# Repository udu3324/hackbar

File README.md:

# hackbar

Hackbar is a macro keys pad in the shape of a bar designed to be placed on the long side of your keyboard. It features 7 switches, an encoder, and two neopixels per key and encoder. It is also inspired by the [Google g-board april fools video](https://www.youtube.com/watch?v=9G3DWHf1xX0). 

# firmware

KMK firmware is used to tell what the mcu sends to the host device when recieving switch inputs. 

# CAD

The cad can be found on [onshape](https://cad.onshape.com/documents/5cba3b888e11db533a85f54f/w/c697cc47e3473bff9588772d/e/0aef22490cba32d3fbb4fb29?renderMode=0&uiState=698d35e3e8867af81a3cb232). 

# Why I Made It

I wanted a macro keyboard that felt like the media control boards used in the a/v industry. They feature toggled leds that are vibrant and bright and look satisfying. I also would like to share this board with some of my friends as its very simple and easy to understand.

# How to Use 

The Seeed Xiao RP2040 makes flashing code very easy through circuitpython on the usb-c. 

# Photos

# Bill of Materials

|Part              |Quantity|On hand|Price |
|------------------|--------|-------|------|
|DSA Keycaps       |7       |no     |      |
|Switches          |7       |no     |      |
|Rotary Encoder Cap|1       |no     |      |
|Rotary Encoder    |1       |no     |      |
|SK6812 MINI-E LEDs|16      |no     |      |
|PCB               |        |no     |$9.55 |
|Seeed XIAO RP2040 |1       |no     |      |
|3d Printed Case   |1       |yes    |      |
|Hot-swap Socket   |7       |yes    |      |

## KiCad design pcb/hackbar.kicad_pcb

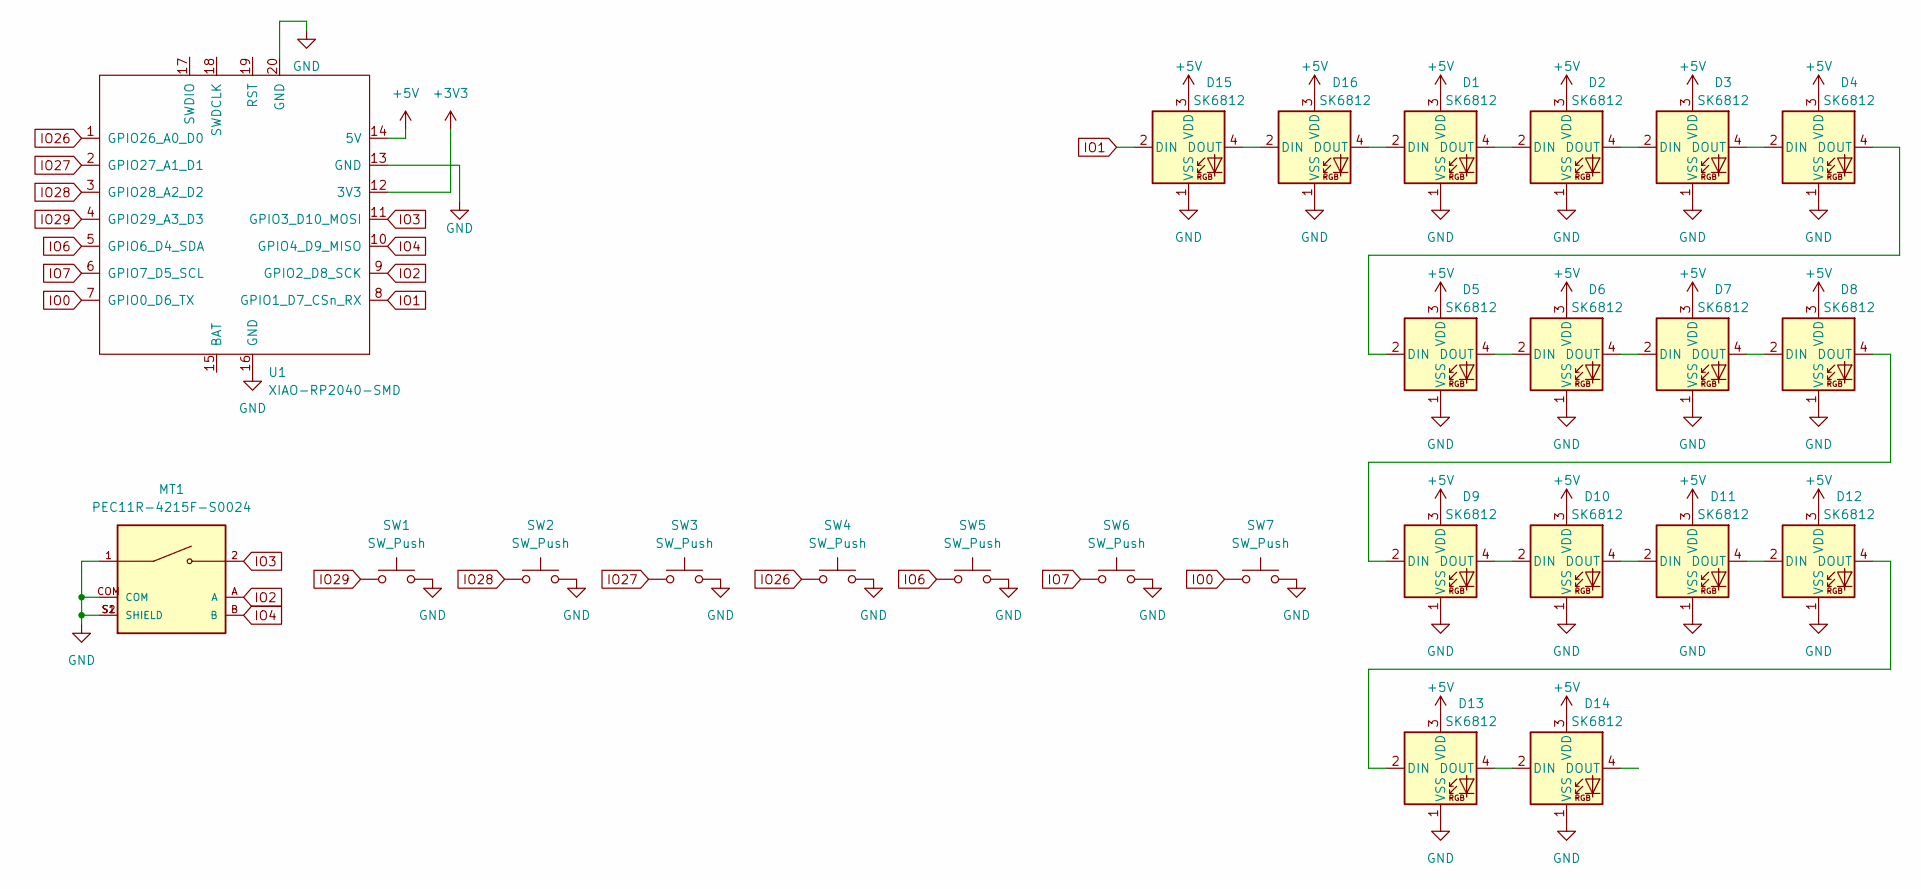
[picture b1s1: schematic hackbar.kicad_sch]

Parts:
D1, D2, D3, D4, D5, D6, D7, D8, D9, D10, D11, D12, D13, D14, D15, D16: SK6812; SK6812MINI-E_fixed
MT1: PEC11R-4215F-S0024; PEC11R-4215F-S0024_XDCR_PEC11R-4215F-S0024; PARTREV Rev. 09/19
SW1, SW2, SW3, SW4, SW5, SW6, SW7: SW_Push; MX-Hotswap-1U
U1: XIAO-RP2040-SMD; XIAO-RP2040-DIP

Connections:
+3V3: U1.12 (3V3)
+5V: D1.3 (VDD), D2.3 (VDD), D3.3 (VDD), D4.3 (VDD), D5.3 (VDD), D6.3 (VDD), D7.3 (VDD), D8.3 (VDD), D9.3 (VDD), D10.3 (VDD), D11.3 (VDD), D12.3 (VDD), D13.3 (VDD), D14.3 (VDD), D15.3 (VDD), D16.3 (VDD), U1.14 (5V)
GND: D1.1 (VSS), D2.1 (VSS), D3.1 (VSS), D4.1 (VSS), D5.1 (VSS), D6.1 (VSS), D7.1 (VSS), D8.1 (VSS), D9.1 (VSS), D10.1 (VSS), D11.1 (VSS), D12.1 (VSS), D13.1 (VSS), D14.1 (VSS), D15.1 (VSS), D16.1 (VSS), MT1.1, MT1.COM, MT1.S1 (SHIELD), MT1.S2 (SHIELD), SW1.2, SW2.2, SW3.2, SW4.2, SW5.2, SW6.2, SW7.2, U1.13 (GND), U1.16 (GND), U1.20 (GND)
IO0: SW7.1, U1.7 (GPIO0_D6_TX)
IO1: D15.2 (DIN), U1.8 (GPIO1_D7_CSn_RX)
IO2: MT1.A, U1.9 (GPIO2_D8_SCK)
IO3: MT1.2, U1.11 (GPIO3_D10_MOSI)
IO4: MT1.B, U1.10 (GPIO4_D9_MISO)
IO6: SW5.1, U1.5 (GPIO6_D4_SDA)
IO7: SW6.1, U1.6 (GPIO7_D5_SCL)
IO26: SW4.1, U1.1 (GPIO26_A0_D0)
IO27: SW3.1, U1.2 (GPIO27_A1_D1)
IO28: SW2.1, U1.3 (GPIO28_A2_D2)
IO29: SW1.1, U1.4 (GPIO29_A3_D3)
unnamed: D1.2 (DIN), D16.4 (DOUT)
unnamed: D1.4 (DOUT), D2.2 (DIN)
unnamed: D2.4 (DOUT), D3.2 (DIN)
unnamed: D3.4 (DOUT), D4.2 (DIN)
unnamed: D4.4 (DOUT), D5.2 (DIN)
unnamed: D5.4 (DOUT), D6.2 (DIN)
unnamed: D6.4 (DOUT), D7.2 (DIN)
unnamed: D7.4 (DOUT), D8.2 (DIN)
unnamed: D8.4 (DOUT), D9.2 (DIN)
unnamed: D9.4 (DOUT), D10.2 (DIN)
unnamed: D10.4 (DOUT), D11.2 (DIN)
unnamed: D11.4 (DOUT), D12.2 (DIN)
unnamed: D12.4 (DOUT), D13.2 (DIN)
unnamed: D13.4 (DOUT), D14.2 (DIN)
unnamed: D15.4 (DOUT), D16.2 (DIN)

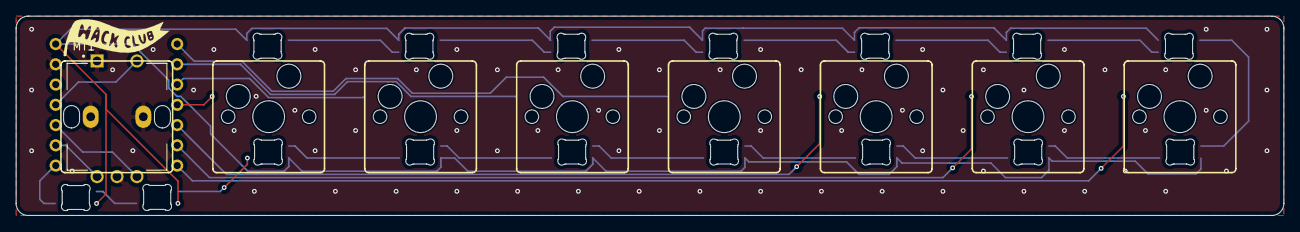
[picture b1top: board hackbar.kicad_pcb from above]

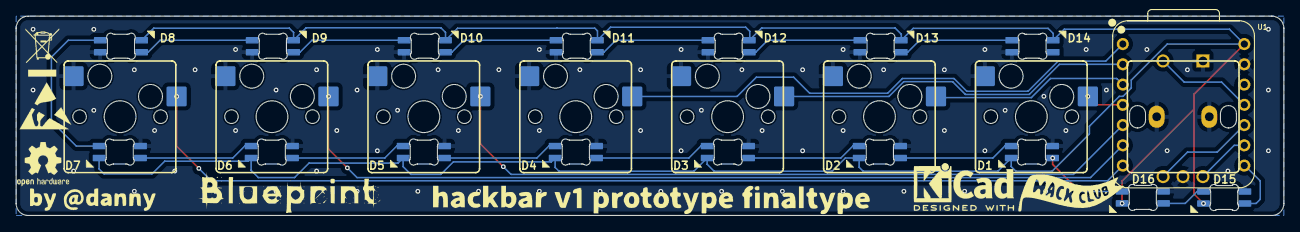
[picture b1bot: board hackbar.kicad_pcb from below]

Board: 2 copper layers, 158.9 x 25.0 mm, 25 parts (8 on the bottom side), 28 nets.

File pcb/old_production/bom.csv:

Designator,Footprint,Quantity,Value,LCSC Part #
"D1, D10, D11, D12, D13, D14, D2, D3, D4, D5, D6, D7, D8, D9",SK6812MINI-E_fixed,14,SK6812,
MT1,PEC11R-4215F-S0024_XDCR_PEC11R-4215F-S0024,1,PEC11R-4215F-S0024,
"SW1, SW2, SW3, SW4, SW5, SW6, SW7",MX-Hotswap-1U,7,SW_Push,
U1,XIAO-RP2040-DIP,1,XIAO-RP2040-SMD,

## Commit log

2026-02-09 initial
2026-02-11 pcb layout + final touches + cad
2026-02-12 add cad, images, readme, bom
2026-02-12 add firmware
2026-02-12 readme update
2026-03-09 add qmk firmware
2026-03-10 better qmk firmware
2026-03-10 add final photo
